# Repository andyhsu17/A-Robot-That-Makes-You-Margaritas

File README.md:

# A-Robot-That-Makes-You-Margaritas

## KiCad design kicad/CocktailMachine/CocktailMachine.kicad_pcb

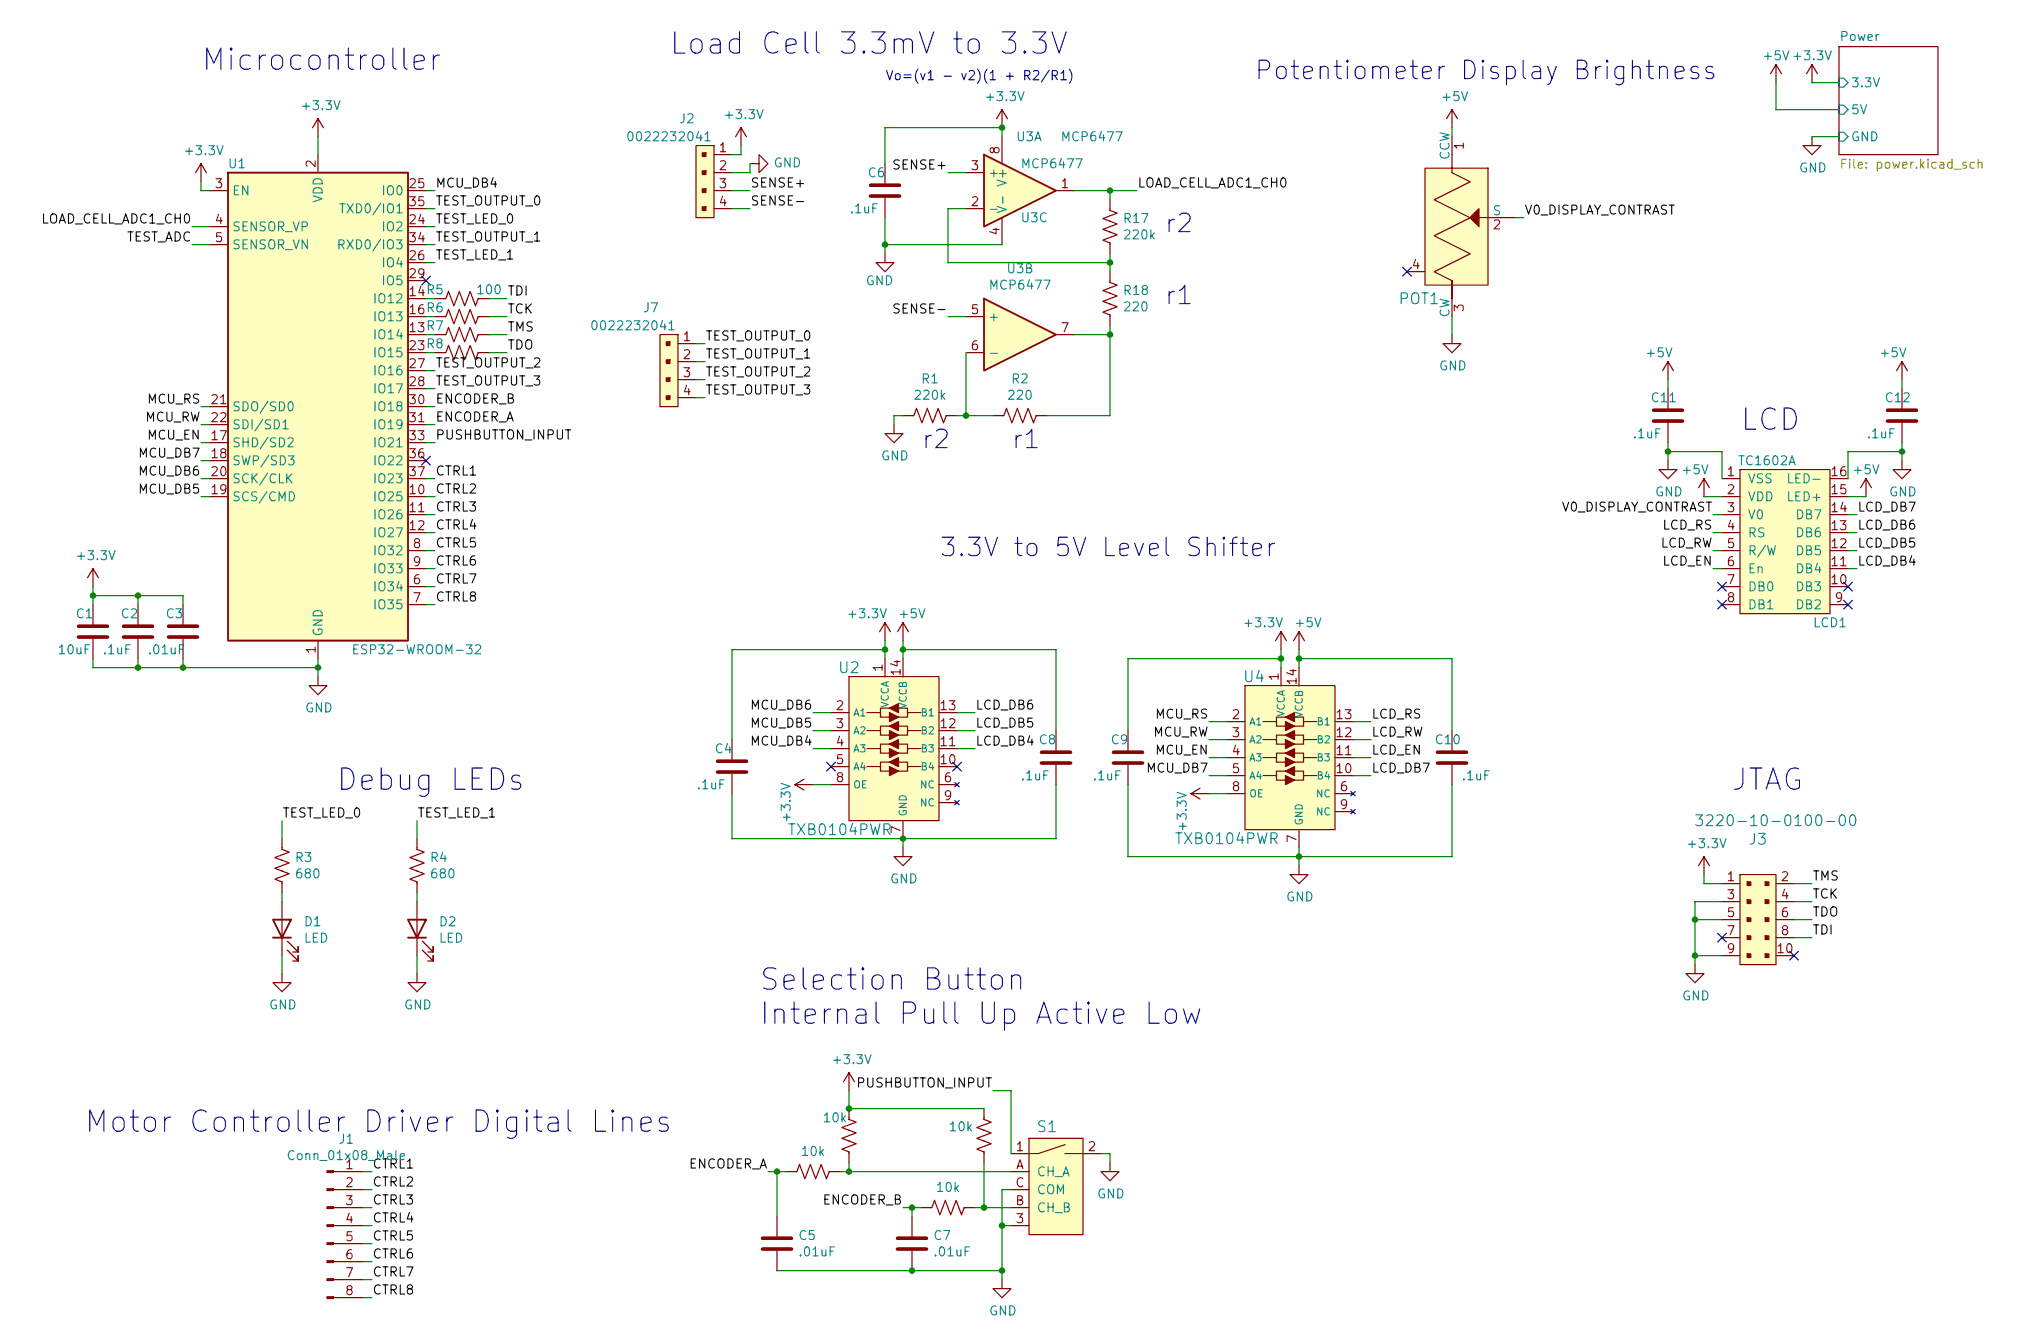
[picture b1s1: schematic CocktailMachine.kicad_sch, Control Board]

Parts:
C1: 10uF; C_0603_1608Metric
C2, C4, C6, C8, C9, C10, C11, C12: .1uF; C_0603_1608Metric
C3, C5, C7: .01uF; C_0603_1608Metric
D1, D2: LED; LED_D3.0mm
J1: Conn_01x08_Male; PinHeader_1x08_P2.54mm_Vertical
J2, J7: 0022232041; PinHeader_1x4_P2.54mm_Drill1.02mm; MPN 0022232041; Digi-Key_PN WM4202-ND
J3: 3220-10-0100-00; PinHeader_2x5_P1.27mm_Drill.7mm; MPN 3220-10-0100-00; Digi-Key_PN 1175-1627-ND
LCD1: TC1602A; TC1062A
POT1: P120PK-Y25BR10K; Potentiometer_P120PK-Y25BR10K; MPN P120PK-Y25BR10K; Digi-Key_PN 987-1710-ND
R1, R17: 220k; R_0603_1608Metric
R2, R18: 220; R_0603_1608Metric
R3, R4: 680; R_0603_1608Metric
R5, R6, R7, R8: 100; R_0603_1608Metric
R9, R10, R11, R12: 10k; R_0603_1608Metric
S1: PEC11R-4215F-S0024; Rotary_Encoder_Switched_PEC11R; MPN PEC11R-4215F-S0024; Digi-Key_PN PEC11R-4215F-S0024-ND
U1: ESP32-WROOM-32
U2, U4: TXB0104PWR; TSSOP-14_W4.4mm; MPN TXB0104PWR; Digi-Key_PN 296-21929-1-ND
U3: MCP6477; MCP6477-MSOP

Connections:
+3V3: C1.1, C2.1, C3.1, C4.1, C6.1, C9.1, J2.1, J3.1, R10.2, R12.2, U1.2 (VDD), U1.3 (EN), U2.1 (VCCA), U2.8 (OE), U3.8 (V+), U4.1 (VCCA), U4.8 (OE); also elsewhere on the board
+5V: C8.1, C10.1, C11.1, C12.1, LCD1.2 (VDD), LCD1.15 (LED+), POT1.1 (CCW), U2.14 (VCCB), U4.14 (VCCB); also elsewhere on the board
/CTRL1: J1.1, U1.37 (IO23)
/CTRL2: J1.2, U1.10 (IO25)
/CTRL3: J1.3, U1.11 (IO26)
/CTRL4: J1.4, U1.12 (IO27)
/CTRL5: J1.5, U1.8 (IO32)
/CTRL6: J1.6, U1.9 (IO33)
/CTRL7: J1.7, U1.6 (IO34)
/CTRL8: J1.8, U1.7 (IO35)
/ENCODER_A: C5.1, R9.2, U1.31 (IO19)
/ENCODER_B: C7.1, R11.2, U1.30 (IO18)
/LCD_DB4: LCD1.11 (DB4), U2.11 (B3)
/LCD_DB5: LCD1.12 (DB5), U2.12 (B2)
/LCD_DB6: LCD1.13 (DB6), U2.13 (B1)
/LCD_DB7: LCD1.14 (DB7), U4.10 (B4)
/LCD_EN: LCD1.6 (En), U4.11 (B3)
/LCD_RS: LCD1.4 (RS), U4.13 (B1)
/LCD_RW: LCD1.5 (R/W), U4.12 (B2)
/LOAD_CELL_ADC1_CH0: R17.1, U1.4 (SENSOR_VP), U3.1
/MCU_DB4: U1.25 (IO0), U2.4 (A3)
/MCU_DB5: U1.19 (SCS/CMD), U2.3 (A2)
/MCU_DB6: U1.20 (SCK/CLK), U2.2 (A1)
/MCU_DB7: U1.18 (SWP/SD3), U4.5 (A4)
/MCU_EN: U1.17 (SHD/SD2), U4.4 (A3)
/MCU_RS: U1.21 (SDO/SD0), U4.2 (A1)
/MCU_RW: U1.22 (SDI/SD1), U4.3 (A2)
/PUSHBUTTON_INPUT: S1.1, U1.33 (IO21)
/SENSE+: J2.3, U3.3 (+)
/SENSE-: J2.4, U3.5 (+)
/TCK: J3.4, R6.1
/TDI: J3.8, R5.1
/TDO: J3.6, R8.1
/TEST_ADC: U1.5 (SENSOR_VN)
/TEST_LED_0: R3.1, U1.24 (IO2)
/TEST_LED_1: R4.1, U1.26 (IO4)
/TEST_OUTPUT_0: J7.1, U1.35 (TXD0/IO1)
/TEST_OUTPUT_1: J7.2, U1.34 (RXD0/IO3)
/TEST_OUTPUT_2: J7.3, U1.27 (IO16)
/TEST_OUTPUT_3: J7.4, U1.28 (IO17)
/TMS: J3.2, R7.1
/V0_DISPLAY_CONTRAST: LCD1.3 (V0), POT1.2 (S)
GND: C1.2, C2.2, C3.2, C4.2, C5.2, C6.2, C7.2, C8.2, C9.2, C10.2, C11.2, C12.2, D1.1 (K), D2.1 (K), J2.2, J3.3, J3.5, J3.9, LCD1.1 (VSS), LCD1.16 (LED-), POT1.3 (CW), R1.2, S1.2, S1.3, S1.C (COM), U1.1 (GND), U1.15 (GND), U1.38 (GND), U1.39 (GND), U2.7 (GND), U3.4 (V-), U4.7 (GND); also elsewhere on the board
unnamed: D1.2 (A), R3.2
unnamed: D2.2 (A), R4.2
unnamed: R1.1, R2.2, U3.6 (-)
unnamed: R5.2, U1.14 (IO12)
unnamed: R6.2, U1.16 (IO13)
unnamed: R7.2, U1.13 (IO14)
unnamed: R8.2, U1.23 (IO15)
unnamed: R9.1, R10.1, S1.A (CH_A)
unnamed: R11.1, R12.1, S1.B (CH_B)
unnamed: R17.2, R18.1, U3.2 (-)
unnamed: R2.1, R18.2, U3.7

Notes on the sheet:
Vo=(v1 - v2)(1 + R2/R1)
LCD
JTAG
Motor Controller Driver Digital Lines
Debug LEDs
Microcontroller
Load Cell 3.3mV to 3.3V
Potentiometer Display Brightness
3.3V to 5V Level Shifter
Selection Button Internal Pull Up Active Low

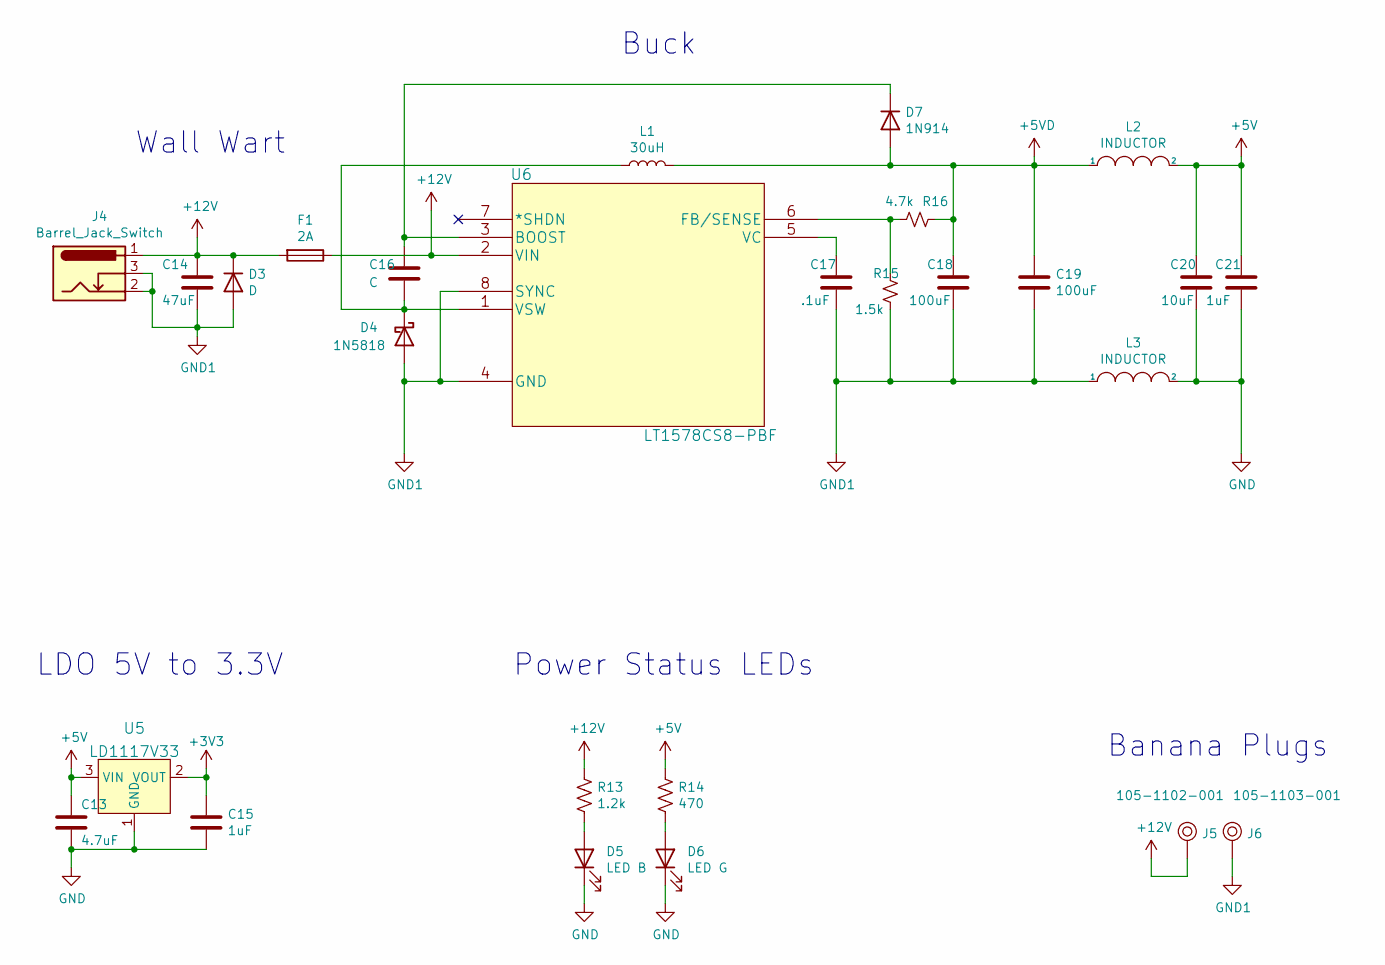
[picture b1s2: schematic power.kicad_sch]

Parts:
C13: 4.7uF; C_0603_1608Metric
C14: 47uF; C_0603_1608Metric
C15, C21: 1uF; C_0603_1608Metric
C16: C; C_0603_1608Metric
C17: .1uF; C_0603_1608Metric
C18, C19: 100uF; C_0603_1608Metric
C20: 10uF; C_0603_1608Metric
D3: D; D_0603_1608Metric
D4: 1N5818; D_DO-41_SOD81_P10.16mm_Horizontal
D5: LED B; LED_D3.0mm
D6: LED G; LED_D3.0mm
D7: 1N914; D_DO-35_SOD27_P7.62mm_Horizontal
F1: 2A; Fuse_0603_1608Metric
J4: Barrel_Jack_Switch; MJ-180PH
J5: 105-1102-001; Test_Jack_Horiz; MPN 105-1102-001; Digi-Key_PN J576-ND
J6: 105-1103-001; Test_Jack_Horiz; MPN 105-1103-001; Digi-Key_PN J577-ND
L1: 30uH; L_0603_1608Metric
L2, L3: INDUCTOR; L_0603_1608Metric
R13: 1.2k; R_0603_1608Metric
R14: 470; R_0603_1608Metric
R15: 1.5k; R_0603_1608Metric
R16: 4.7k; R_0603_1608Metric
U5: LD1117V33; TO-220-3; MPN LD1117V33; Digi-Key_PN 497-1491-5-ND
U6: LT1578CS8-PBF

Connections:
+3V3: C15.1, U5.2 (VOUT); also elsewhere on the board
+5V: C13.1, C20.1, C21.1, L2.2, R14.1, U5.3 (VIN); also elsewhere on the board
+5VD: C18.1, C19.1, D7.2 (A), L1.2, L2.1, R16.1
+12V: C14.1, D3.1 (K), F1.1, F1.2, J4.1, J5.1, R13.1, U6.2 (VIN)
GND: C13.2, C15.2, C20.2, C21.2, D5.1 (K), D6.1 (K), L3.2, U5.1 (GND); also elsewhere on the board
GND1: C14.2, C17.2, C18.2, C19.2, D3.2 (A), D4.2 (A), J4.2, J4.3, J6.1, L3.1, R15.1, U6.4 (GND), U6.8 (SYNC)
unnamed: C16.1, D7.1 (K), U6.3 (BOOST)
unnamed: C16.2, D4.1 (K), L1.1, U6.1 (VSW)
unnamed: C17.1, U6.5 (VC)
unnamed: D5.2 (A), R13.2
unnamed: D6.2 (A), R14.2
unnamed: R15.2, R16.2, U6.6 (FB/SENSE)

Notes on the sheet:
Buck
Banana Plugs
Power Status LEDs
Wall Wart
LDO 5V to 3.3V

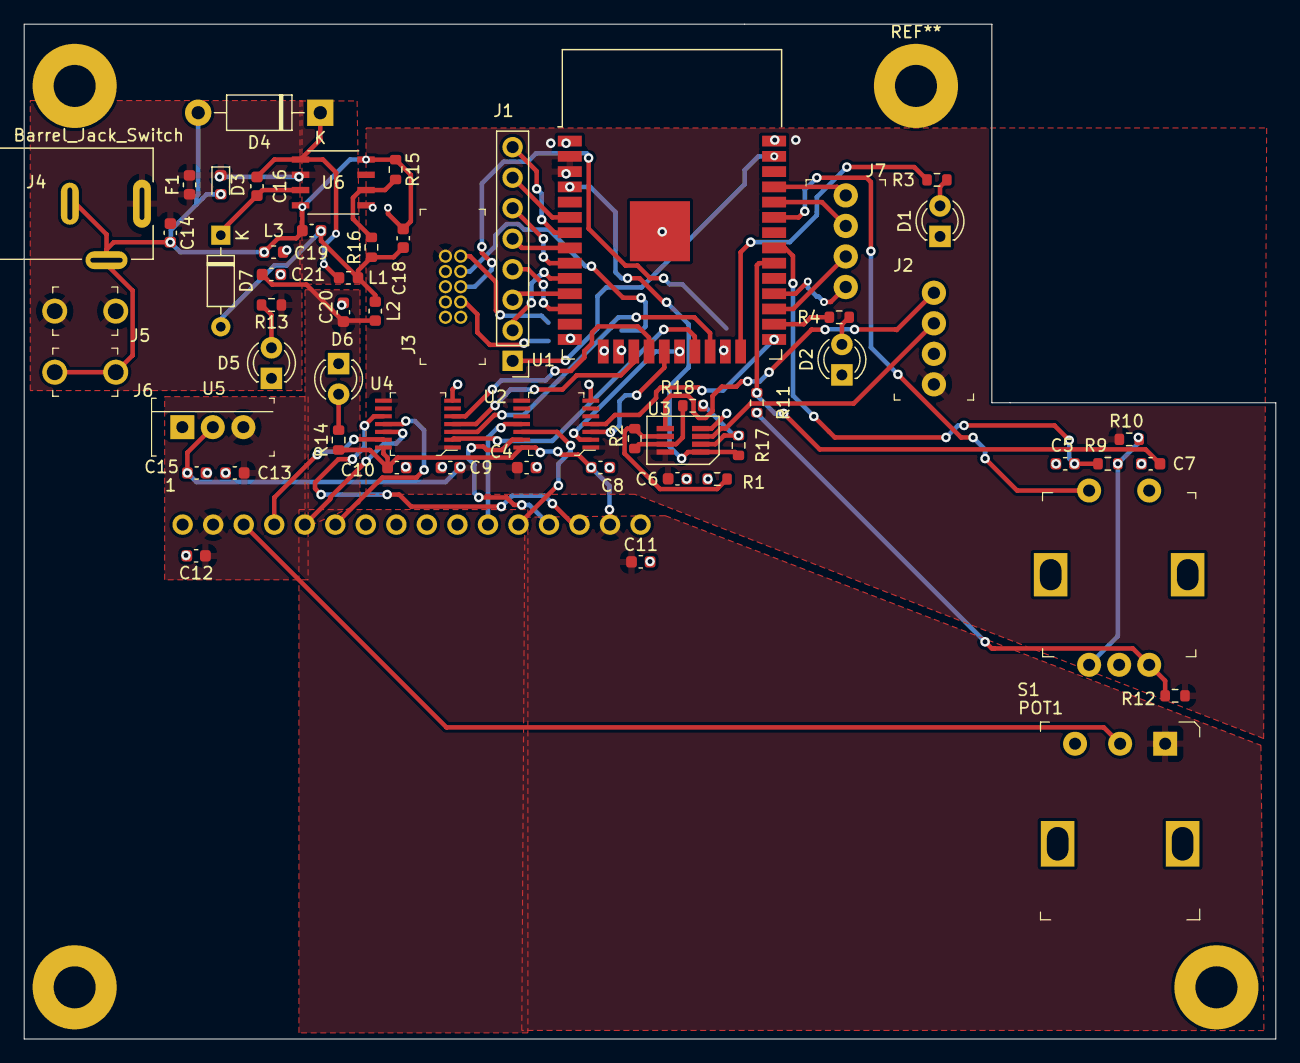
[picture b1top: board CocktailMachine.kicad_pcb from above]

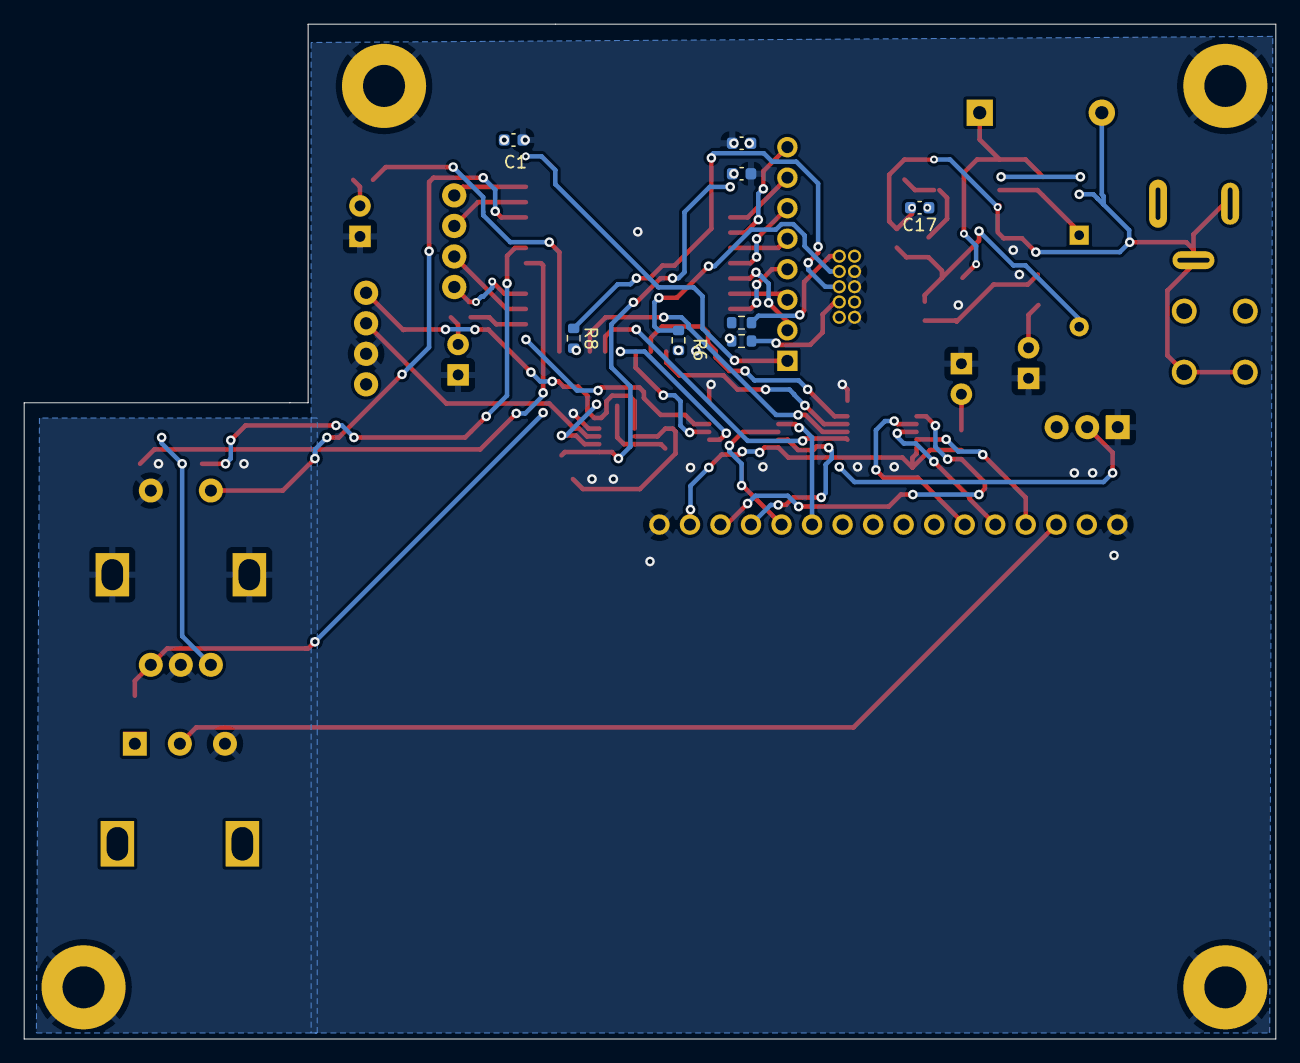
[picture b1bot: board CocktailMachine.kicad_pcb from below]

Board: 2 copper layers, 104.1 x 84.4 mm, 66 parts (8 on the bottom side), 62 nets.

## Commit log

2021-10-09 Draft 1: Missing footprints
2021-10-24 - Add decoupling for all ICs - Separate power planes from buck for noise reduction - Miscellaneous fixes
2021-10-24 quick fix to dual op amp package
2021-12-04 Generate footprints and netlist. Begin Layout.
2021-12-04 Add extra pin headers before layout
2022-02-21 - Update symbol and footprint library - Update obsolete components - Initial layout positioning done. Todo: routing
2022-02-22 - Fix DRC violations - Shrink space between modules to reduce board size
2022-03-11 - Finish layout - Fixed all DRC violations minus silkscreen issues - Updated via sizes to meet PCBWay requirements
2022-03-23 - Polygon pour zones for 3V3, 12V, and 5V - Add mounting holes - Finish routing and change to all 15 mil track widths
2022-03-27 Add gerber and drill files
2022-03-29 Fix footprint issue
2022-04-10 Generate new gerbers

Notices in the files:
parts and their libraries:
Copyright 2021 Accelerated Designs. All rights reserved.
